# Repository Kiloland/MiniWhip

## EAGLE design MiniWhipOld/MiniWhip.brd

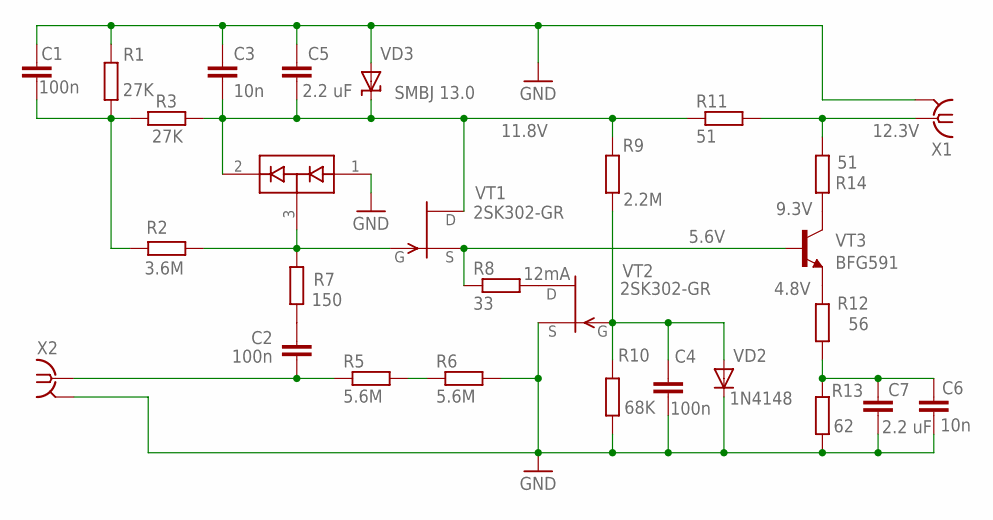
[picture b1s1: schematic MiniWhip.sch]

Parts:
C1, C2, C4: 100n; C0603
C3, C6: 10n; C0603
C5, C7: 2.2 uF; C0603
R1, R3: 27K; R0603
R2: 3.6M; R0805
R5, R6: 5.6M; R0805
R7: 150; R0805
R8: 33; R0805
R9: 2.2M; R0603
R10: 68K; R0603
R11, R14: 51; R0603
R12: 56; R0603
R13: 62; R0603
VD1: BAV99; SOT23
VD2: 1N4148; SOD80C
VD3: SMBJ 13.0; SMBJ
VT1, VT2: 2SK302SOT23; SOT23
VT3: BFG591; SOT223
X1, X2: SMA-142-0701-801/806; J502-ND-142-0701-801/806

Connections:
+12V: C3.2, C5.2, R3.2, R9.2, R11.1, VD1.2 (C2), VD3.C, VT1.1 (D)
GND: C1.1, C3.1, C4.2, C5.1, C6.2, C7.2, R1.2, R6.2, R10.1, R13.1, VD1.1 (A1), VD2.C, VD3.A, VT2.3 (S), X1.G@1 (2), X1.G@2 (2), X1.G@3 (2), X1.G@4 (2), X2.G@1 (2), X2.G@2 (2), X2.G@3 (2), X2.G@4 (2)
IN: C2.2, R5.1, X2.1
unnamed: C1.2, R1.1, R2.1, R3.1
unnamed: R14.2, VT3.4 (C)
unnamed: R2.2, R7.1, VD1.3 (COM), VT1.2 (G)
unnamed: C6.1, C7.1, R12.1, R13.2
unnamed: R12.2, VT3.1 (E), VT3.3 (E)
unnamed: R8.2, VT2.1 (D)
unnamed: C4.1, R9.1, R10.2, VD2.A, VT2.2 (G)
unnamed: C2.1, R7.2
unnamed: R5.2, R6.1
OUT: R11.2, R14.1, X1.1
PREAMP: R8.1, VT1.3 (S), VT3.2 (B)

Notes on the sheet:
2SK302-GR
12.3V
9.3V
11.8V
12mA
4.8V
5.6V

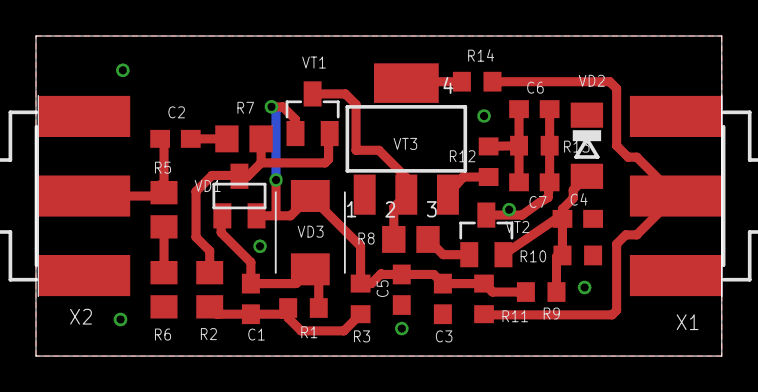
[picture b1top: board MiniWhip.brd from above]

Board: 2 copper layers, 38.1 x 17.8 mm, 28 parts (0 on the bottom side), 14 nets.

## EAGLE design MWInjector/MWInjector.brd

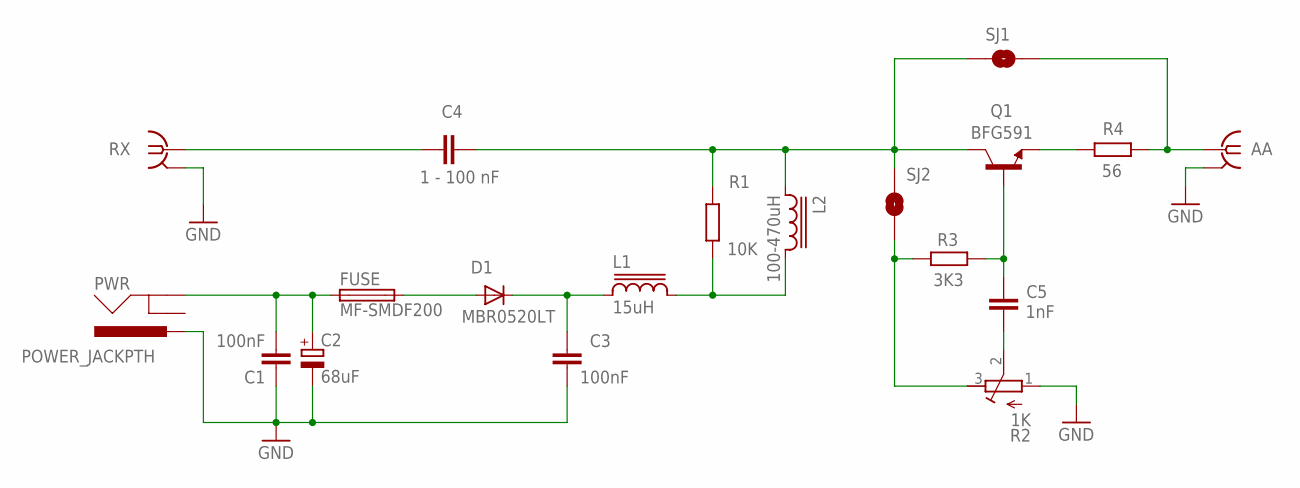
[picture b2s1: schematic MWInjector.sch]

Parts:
AA: SMA-142-0701-851/861; J502-ND-142-0701-851/861
C1, C3: 100nF; C1206
C2: 68uF; SMC_C
C4: 1 - 100 nF; C1206
C5: 1nF; C1206
D1: MBR0520LT; SOD123
FUSE: MF-SMDF200; MF-SMDF050
L1: 15uH; CDRH6D
L2: 100-470uH; CDRH104R
PWR: POWER_JACKPTH; POWER_JACK_PTH
Q1: BFG591; SOT223
R1: 10K; R1206
R2: 1K; RTRIM3202
R3: 3K3; R1206
R4: 56; R2512
RX: SMA-142-0701-851/861; J502-ND-142-0701-851/861
SJ1, SJ2: SOLDERJUMPERNO; SJ_2S-NO

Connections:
+12V: C1.2, C2.+, FUSE.1, PWR.GND
GND: AA.G@1 (2), AA.G@2 (2), AA.G@3 (2), AA.G@4 (2), C1.1, C2.-, C3.1, PWR.PWR, R2.1 (A), RX.G@1 (2), RX.G@2 (2), RX.G@3 (2), RX.G@4 (2)
unnamed: R2.3 (E), R3.1, SJ2.1
unnamed: D1.A, FUSE.2
unnamed: C4.2, RX.1
unnamed: C4.1, L2.1, Q1.4 (C), R1.1, SJ1.1, SJ2.2
unnamed: L1.2, L2.2, R1.2
unnamed: C3.2, D1.C, L1.1
unnamed: Q1.1 (E), Q1.3 (E), R4.1
unnamed: C5.2, Q1.2 (B), R3.2
unnamed: C5.1, R2.2 (S)
unnamed: AA.1, R4.2, SJ1.2

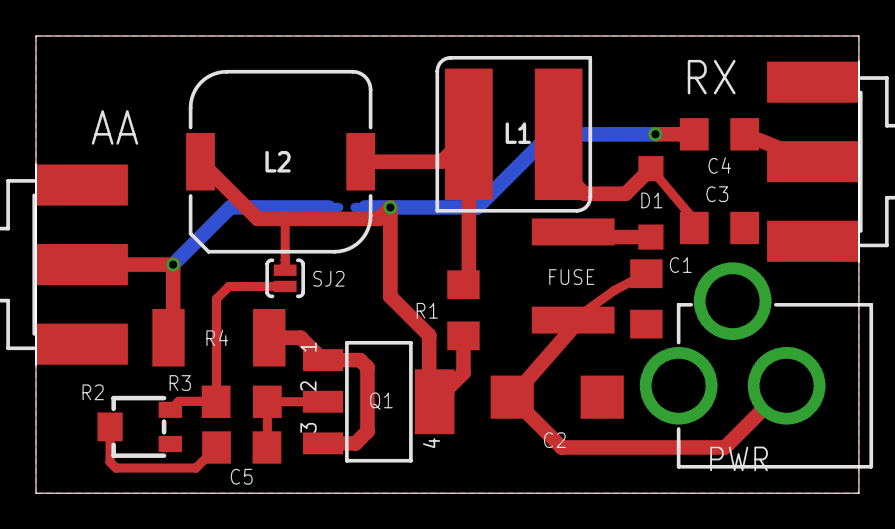
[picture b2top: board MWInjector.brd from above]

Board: 2 copper layers, 45.7 x 25.4 mm, 19 parts (1 on the bottom side), 12 nets.

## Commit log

2018-03-06 Initial version of mini-whip
    original idea from http://www.radioscanner.ru/forum/topic27416-169.html
2018-03-06 updaing names
    MiniWhip -> MiniWhipOld
    MiniWhipNext -> MiniWhip

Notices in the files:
parts and their libraries:
SparkFun-Connectors: Licensing: CC v3.0 Share-Alike You are welcome to use this library for commercial purposes.
inductor-sumida: Copyright (C) 2008, Bob Starr
